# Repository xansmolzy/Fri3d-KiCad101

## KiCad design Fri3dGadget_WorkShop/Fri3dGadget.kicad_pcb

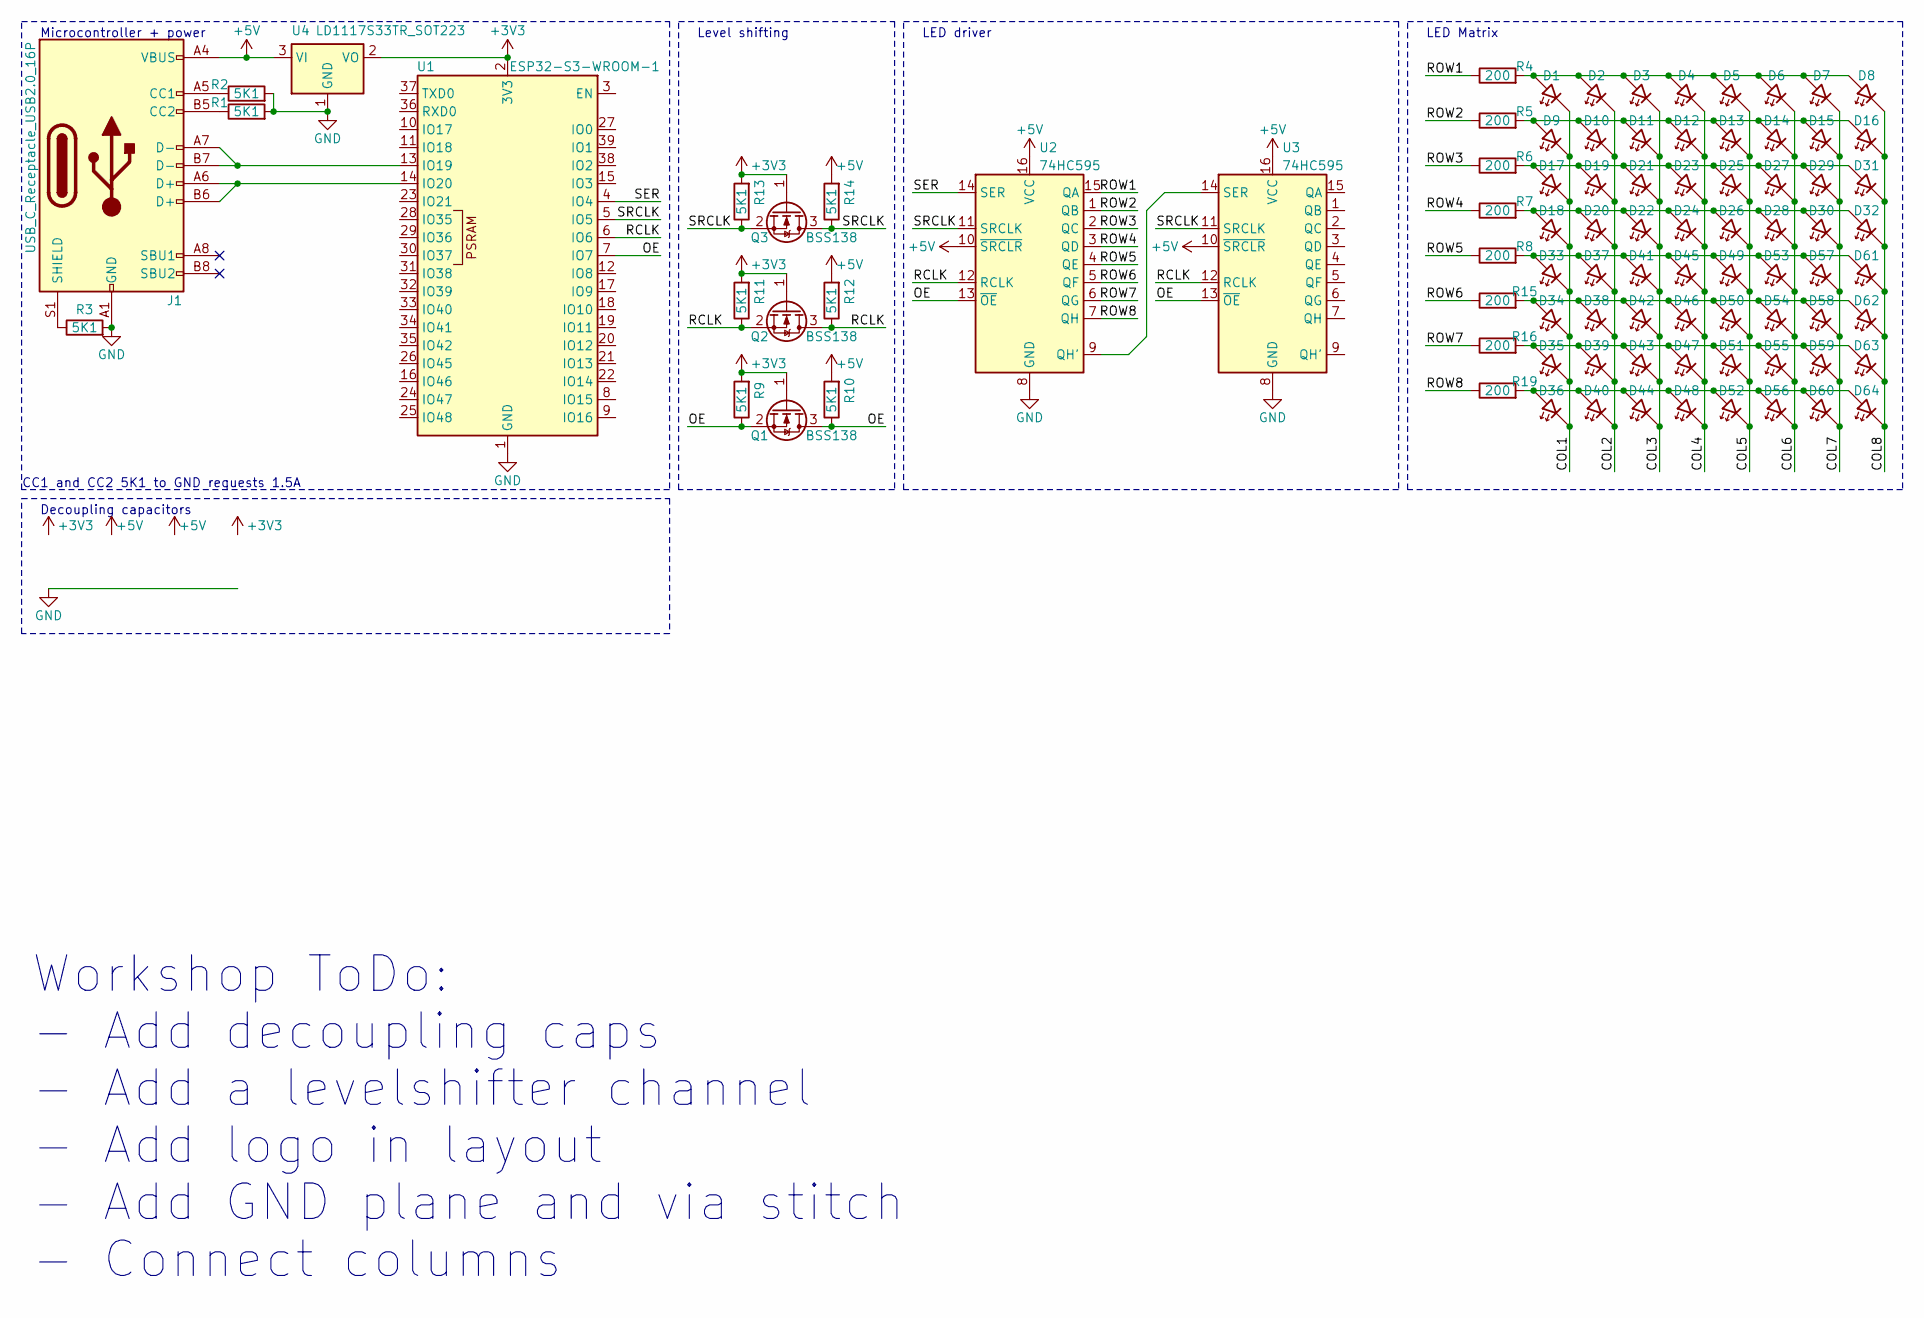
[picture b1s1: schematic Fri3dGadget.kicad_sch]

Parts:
D1, D2, D3, D4, D5, D6, D7, D8, D9, D10, D11, D12, D13, D14, D15, D16, D17, D18, D19, D20, D21, D22, D23, D24, D25, D26, D27, D28, D29, D30, D31, D32, D33, D34, D35, D36, D37, D38, D39, D40, D41, D42, D43, D44, D45, D46, D47, D48, D49, D50, D51, D52, D53, D54, D55, D56, D57, D58, D59, D60, D61, D62, D63, D64: LED_45deg; LED_0805_2012Metric
J1: USB_C_Receptacle_USB2.0_16P; USB_C_Receptacle_HCTL_HC-TYPE-C-16P-01A
Q1, Q2, Q3: BSS138; SOT-23
R1, R2, R3, R9, R10, R11, R12, R13, R14: 5K1; R_0805_2012Metric
R4, R5, R6, R7, R8, R15, R16, R19: 200; R_0805_2012Metric
U1: ESP32-S3-WROOM-1
U2, U3: 74HC595; SOIC-16_3.9x9.9mm_P1.27mm
U4: LD1117S33TR_SOT223; SOT-223-3_TabPin2

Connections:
+3V3: Q1.1 (G), Q2.1 (G), Q3.1 (G), R9.2, R11.2, R13.2, U1.2 (3V3), U4.2 (VO)
+5V: J1.A4 (VBUS), J1.A9 (VBUS), J1.B4 (VBUS), J1.B9 (VBUS), R10.2, R12.2, R14.2, U2.10 (~SRCLR), U2.16 (VCC), U3.10 (~SRCLR), U3.16 (VCC), U4.3 (VI); also elsewhere on the board
/COL1: D1.1 (K), D9.1 (K), D17.1 (K), D18.1 (K), D33.1 (K), D34.1 (K), D35.1 (K), D36.1 (K), U3.15 (QA)
/COL2: D2.1 (K), D10.1 (K), D19.1 (K), D20.1 (K), D37.1 (K), D38.1 (K), D39.1 (K), D40.1 (K), U3.1 (QB)
/COL3: D3.1 (K), D11.1 (K), D21.1 (K), D22.1 (K), D41.1 (K), D42.1 (K), D43.1 (K), D44.1 (K), U3.2 (QC)
/COL4: D4.1 (K), D12.1 (K), D23.1 (K), D24.1 (K), D45.1 (K), D46.1 (K), D47.1 (K), D48.1 (K), U3.3 (QD)
/COL5: D5.1 (K), D13.1 (K), D25.1 (K), D26.1 (K), D49.1 (K), D50.1 (K), D51.1 (K), D52.1 (K), U3.4 (QE)
/COL6: D6.1 (K), D14.1 (K), D27.1 (K), D28.1 (K), D53.1 (K), D54.1 (K), D55.1 (K), D56.1 (K), U3.5 (QF)
/COL7: D7.1 (K), D15.1 (K), D29.1 (K), D30.1 (K), D57.1 (K), D58.1 (K), D59.1 (K), D60.1 (K), U3.6 (QG)
/COL8: D8.1 (K), D16.1 (K), D31.1 (K), D32.1 (K), D61.1 (K), D62.1 (K), D63.1 (K), D64.1 (K), U3.7 (QH)
/OE: Q1.2 (S), Q1.3 (D), R9.1, R10.1, U1.7 (IO7), U2.13 (~OE), U3.13 (~OE)
/RCLK: Q2.2 (S), Q2.3 (D), R11.1, R12.1, U1.6 (IO6), U2.12 (RCLK), U3.12 (RCLK)
/ROW1: R4.1, U2.15 (QA)
/ROW2: R5.1, U2.1 (QB)
/ROW3: R6.1, U2.2 (QC)
/ROW4: R7.1, U2.3 (QD)
/ROW5: R8.1, U2.4 (QE)
/ROW6: R15.1, U2.5 (QF)
/ROW7: R16.1, U2.6 (QG)
/ROW8: R19.1, U2.7 (QH)
/SER: U1.4 (IO4), U2.14 (SER)
/SRCLK: Q3.2 (S), Q3.3 (D), R13.1, R14.1, U1.5 (IO5), U2.11 (SRCLK), U3.11 (SRCLK)
GND: J1.A1 (GND), J1.A12 (GND), J1.B1 (GND), J1.B12 (GND), R1.2, R2.2, R3.2, U1.1 (GND), U1.40 (GND), U1.41 (GND), U2.8 (GND), U3.8 (GND), U4.1 (GND); also elsewhere on the board
unnamed: D1.2 (A), D2.2 (A), D3.2 (A), D4.2 (A), D5.2 (A), D6.2 (A), D7.2 (A), D8.2 (A), R4.2
unnamed: D9.2 (A), D10.2 (A), D11.2 (A), D12.2 (A), D13.2 (A), D14.2 (A), D15.2 (A), D16.2 (A), R5.2
unnamed: D17.2 (A), D19.2 (A), D21.2 (A), D23.2 (A), D25.2 (A), D27.2 (A), D29.2 (A), D31.2 (A), R6.2
unnamed: D18.2 (A), D20.2 (A), D22.2 (A), D24.2 (A), D26.2 (A), D28.2 (A), D30.2 (A), D32.2 (A), R7.2
unnamed: D33.2 (A), D37.2 (A), D41.2 (A), D45.2 (A), D49.2 (A), D53.2 (A), D57.2 (A), D61.2 (A), R8.2
unnamed: D34.2 (A), D38.2 (A), D42.2 (A), D46.2 (A), D50.2 (A), D54.2 (A), D58.2 (A), D62.2 (A), R15.2
unnamed: D35.2 (A), D39.2 (A), D43.2 (A), D47.2 (A), D51.2 (A), D55.2 (A), D59.2 (A), D63.2 (A), R16.2
unnamed: D36.2 (A), D40.2 (A), D44.2 (A), D48.2 (A), D52.2 (A), D56.2 (A), D60.2 (A), D64.2 (A), R19.2
unnamed: J1.A5 (CC1), R2.1
unnamed: J1.B5 (CC2), R1.1
unnamed: J1.S1 (SHIELD), R3.1
unnamed: J1.A7 (D-), J1.B7 (D-), U1.13 (IO19)
unnamed: J1.A6 (D+), J1.B6 (D+), U1.14 (IO20)
unnamed: U2.9 (QH'), U3.14 (SER)

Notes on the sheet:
Level shifting
LED driver
CC1 and CC2 5K1 to GND requests 1.5A
Workshop ToDo: - Add decoupling caps - Add a levelshifter channel - Add logo in layout - Add GND plane and via stitch - Connect columns
Decoupling capacitors
Microcontroller + power
LED Matrix

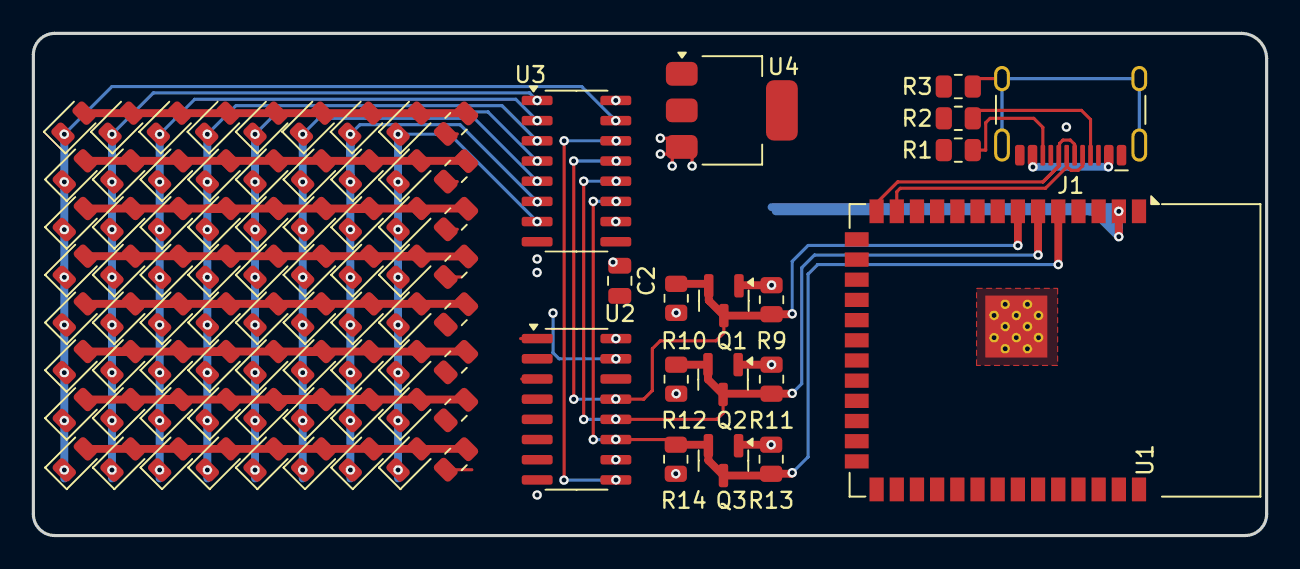
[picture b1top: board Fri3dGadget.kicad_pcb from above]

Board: 2 copper layers, 77.6 x 31.6 mm, 90 parts (0 on the bottom side), 37 nets.

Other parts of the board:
C2: 4.7u; C_0805_2012Metric

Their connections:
+5V: C2.1; also elsewhere on the board
GND: C2.2; also elsewhere on the board

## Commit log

2024-08-16 update slides
